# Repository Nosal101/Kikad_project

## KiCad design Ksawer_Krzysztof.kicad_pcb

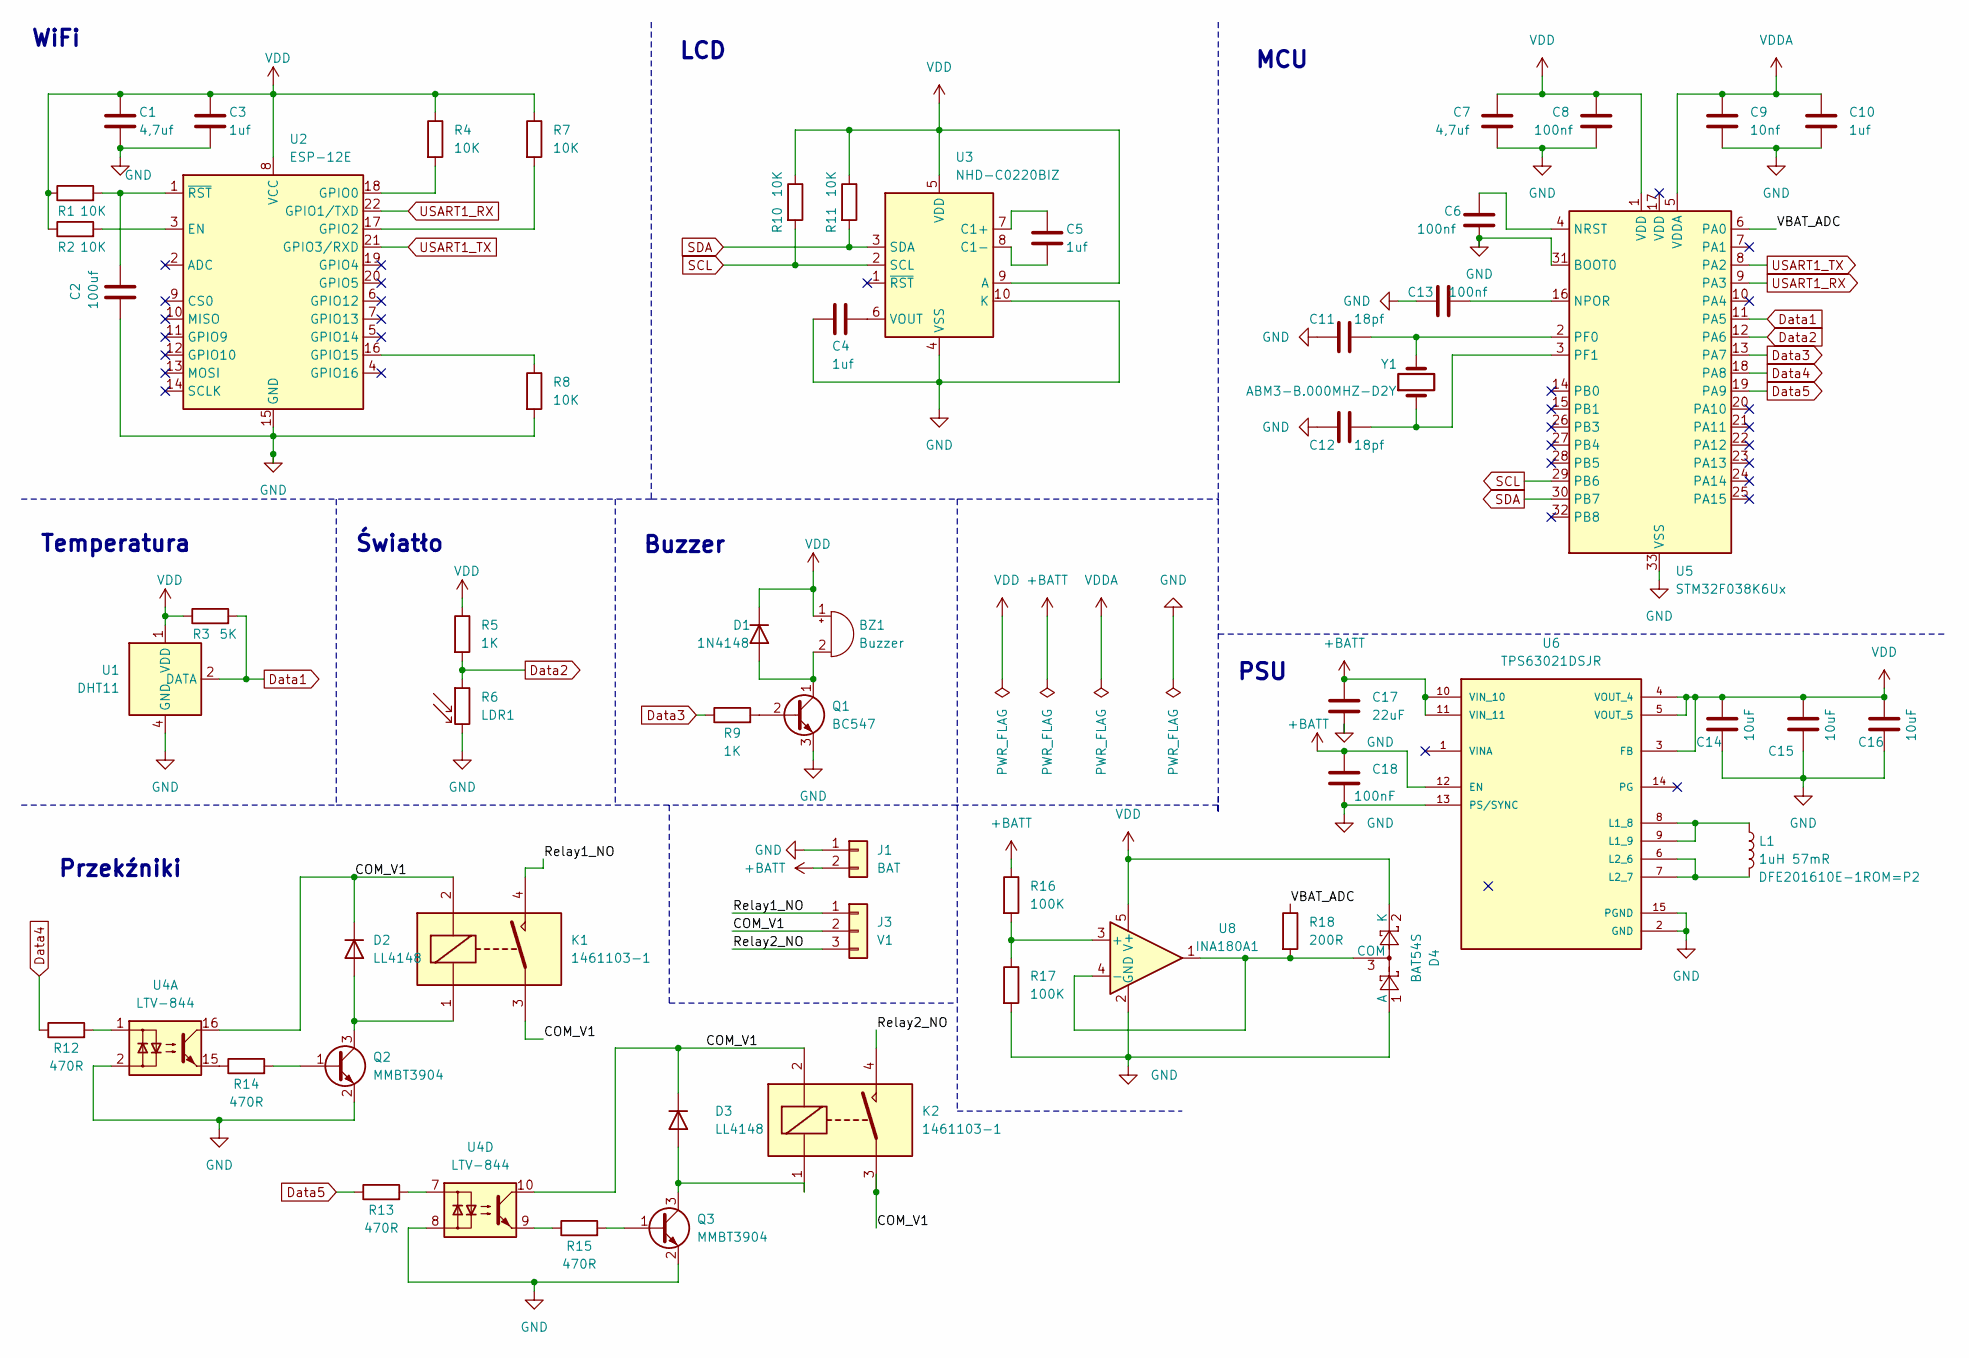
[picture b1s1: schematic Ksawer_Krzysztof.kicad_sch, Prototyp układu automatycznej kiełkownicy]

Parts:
BZ1: Buzzer; Buzzer_12x9.5RM7.6
C1, C7: 4,7uf; C_0603_1608Metric_Pad1.08x0.95mm_HandSolder
C2: 100uf; C_0603_1608Metric_Pad1.08x0.95mm_HandSolder
C3, C4, C5, C10: 1uf; C_0603_1608Metric_Pad1.08x0.95mm_HandSolder
C6, C8, C13: 100nf; C_0603_1608Metric_Pad1.08x0.95mm_HandSolder
C9: 10nf; C_0603_1608Metric_Pad1.08x0.95mm_HandSolder
C11, C12: 18pf; C_0603_1608Metric_Pad1.08x0.95mm_HandSolder
C14, C15, C16: 10uF; C_0603_1608Metric_Pad1.08x0.95mm_HandSolder
C17: 22uF; C_0603_1608Metric_Pad1.08x0.95mm_HandSolder
C18: 100nF; C_0603_1608Metric_Pad1.08x0.95mm_HandSolder
D1: 1N4148; D_DO-35_SOD27_P7.62mm_Horizontal
D2, D3: LL4148; D_MiniMELF
D4: BAT54S; SOT-23
J1: BAT; PinHeader_1x02_P1.00mm_Vertical
J3: V1; PinHeader_1x03_P1.00mm_Vertical
K1, K2: 1461103-1; OJ_OJE_Relay
L1: 1uH 57mR; L_0603_1608Metric
Q1: BC547; TO-92_Inline
Q2, Q3: MMBT3904; SOT-23
R1, R2, R4, R7, R8, R10, R11: 10K; R_0805_2012Metric
R3: 5K; R_0805_2012Metric
R5, R9: 1K; R_0805_2012Metric
R6: LDR1; LDR
R12, R13, R14, R15: 470R; R_0805_2012Metric
R16, R17: 100K; R_0805_2012Metric
R18: 200R; R_0805_2012Metric
U1: DHT11; Aosong_DHT11_5.5x12.0_P2.54mm
U2: ESP-12E
U3: NHD-C0220BIZ; NHD-C0220BiZ
U4: LTV-844; SSO-16_P2.54
U5: STM32F038K6Ux; QFN-32-1EP_5x5mm_P0.5mm_EP3.45x3.45mm
U6: TPS63021DSJR; IC_TPS63021DSJR; PARTREV I
U8: INA180A1; SOT-23-5
Y1: ABM3-B.000MHZ-D2Y; Crystal_SMD_5032-2Pin_5.0x3.2mm

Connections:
+BATT: C17.1, C18.1, J1.2, R16.1, U6.10 (VIN_10), U6.11 (VIN_11), U6.12 (EN)
/COM_V1: D2.1 (K), D3.1 (K), J3.2, K1.2, K1.3, K2.2, K2.3, U4.10, U4.16
/Relay1_NO: J3.1, K1.4
/Relay2_NO: J3.3, K2.4
/VBAT_ADC: R18.1, U5.6 (PA0)
Data1: R3.2, U1.2 (DATA), U5.11 (PA5)
Data2: R5.2, R6.1, U5.12 (PA6)
Data3: R9.1, U5.13 (PA7)
Data4: R12.1, U5.18 (PA8)
Data5: R13.1, U5.19 (PA9)
GND: C1.2, C2.2, C3.2, C4.2, C6.2, C7.2, C8.2, C9.2, C10.2, C11.2, C12.2, C13.1, C14.2, C15.2, C16.2, C17.2, C18.2, D4.1 (A), J1.1, Q1.3 (E), Q2.2 (E), Q3.2 (E), R6.2, R8.2, R17.2, U1.4 (GND), U2.15 (GND), U3.4 (VSS), U3.10 (K), U4.2, U4.8, U5.31 (BOOT0), U5.33 (VSS), U6.2 (GND), U6.13 (PS/SYNC), U6.15 (PGND), U8.2 (GND)
unnamed: BZ1.2 (+), D1.2 (A), Q1.1 (C)
unnamed: D2.2 (A), K1.1, Q2.3 (C)
unnamed: D3.2 (A), K2.1, Q3.3 (C)
unnamed: D4.3 (COM), R18.2, U8.1, U8.4 (-)
unnamed: Q1.2 (B), R9.2
unnamed: Q2.1 (B), R14.2
unnamed: Q3.1 (B), R15.2
unnamed: R12.2, U4.1
unnamed: R13.2, U4.7
unnamed: R14.1, U4.15
unnamed: R15.1, U4.9
unnamed: R2.2, U2.3 (EN)
unnamed: R4.2, U2.18 (GPIO0)
unnamed: R7.2, U2.17 (GPIO2)
unnamed: R8.1, U2.16 (GPIO15)
unnamed: C2.1, R1.2, U2.1 (~RST)
unnamed: C5.1, U3.7 (C1+)
unnamed: C5.2, U3.8 (C1-)
unnamed: C4.1, U3.6 (VOUT)
unnamed: C13.2, U5.16 (NPOR)
unnamed: C6.1, U5.4 (NRST)
unnamed: C11.1, U5.2 (PF0), Y1.2
unnamed: C12.1, U5.3 (PF1), Y1.1
unnamed: L1.1, U6.8 (L1_8), U6.9 (L1_9)
unnamed: L1.2, U6.6 (L2_6), U6.7 (L2_7)
unnamed: R16.2, R17.1, U8.3 (+)
SCL: R10.2, U3.2 (SCL), U5.29 (PB6)
SDA: R11.2, U3.3 (SDA), U5.30 (PB7)
USART1_RX: U2.22 (GPIO1/TXD), U5.9 (PA3)
USART1_TX: U2.21 (GPIO3/RXD), U5.8 (PA2)
VDD: BZ1.1 (-), C1.1, C3.1, C7.1, C8.1, C14.1, C15.1, C16.1, D1.1 (K), D4.2 (K), R1.1, R2.1, R3.1, R4.1, R5.1, R7.1, R10.1, R11.1, U1.1 (VDD), U2.8 (VCC), U3.5 (VDD), U3.9 (A), U5.1 (VDD), U6.3 (FB), U6.4 (VOUT_4), U6.5 (VOUT_5), U8.5 (V+)
VDDA: C9.1, C10.1, U5.5 (VDDA)

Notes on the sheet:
PSU
Przekźniki
LCD
Światło
Temperatura
WiFi
Buzzer
MCU

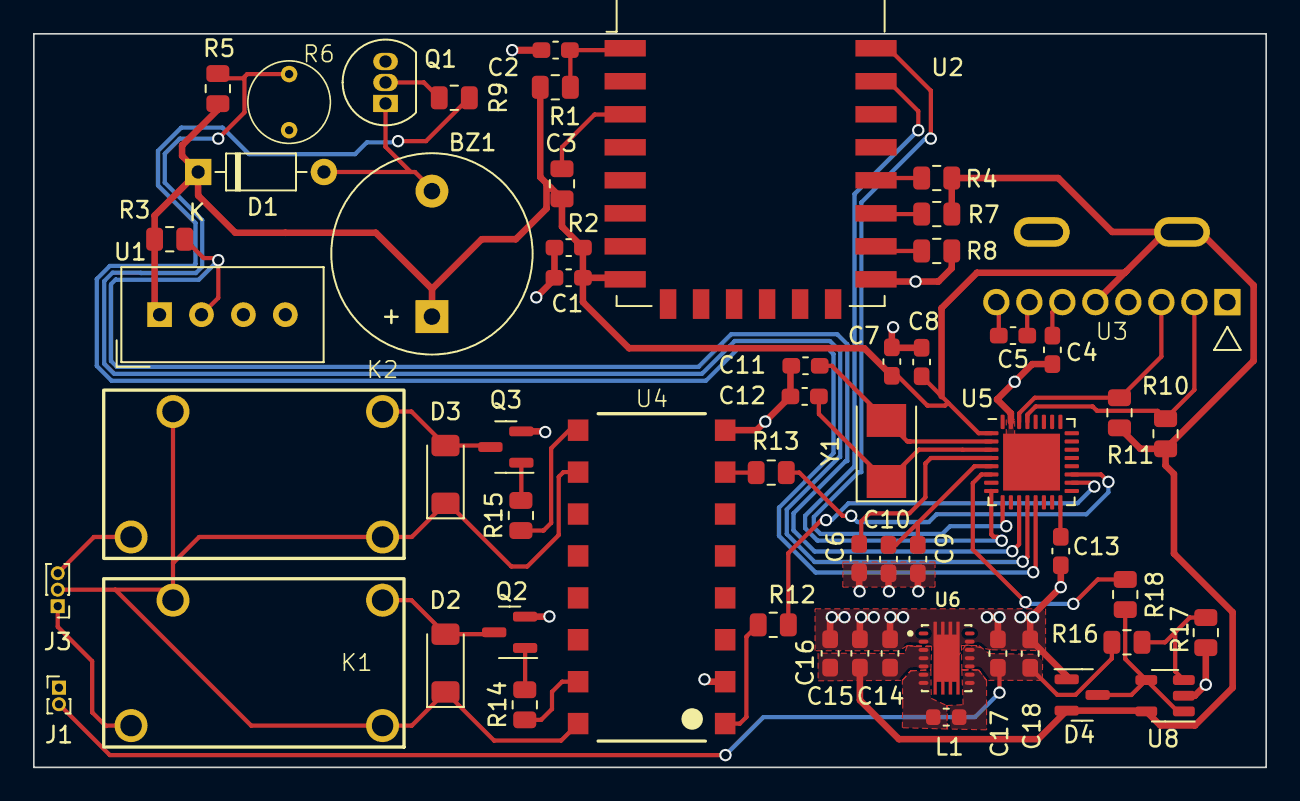
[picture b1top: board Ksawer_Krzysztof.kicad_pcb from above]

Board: 2 copper layers, 74.7 x 44.5 mm, 57 parts (0 on the bottom side), 43 nets.

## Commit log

2023-11-20 First verion
2023-11-25 ślady stoopek
    Dwa slady w przekaźnikach, są jakieś ostrzeżenia
2023-11-27 zmiany2
2023-11-27 zmiana3
2023-11-27 koniec bez błedów
    koniec bez błedów
2023-11-27 zmiana4
2023-11-27 zmiany
2023-11-30 lab3
    lab3
2023-11-30 wstepnie ulozona
2023-12-01 pierwsze laczenia
2023-12-01 polaczenia ale nie wiem czy to wg ma sens
2023-12-10 prawie koniec
2023-12-16 warstwa
2023-12-16 maslo
2023-12-17 gotowy_projekt
